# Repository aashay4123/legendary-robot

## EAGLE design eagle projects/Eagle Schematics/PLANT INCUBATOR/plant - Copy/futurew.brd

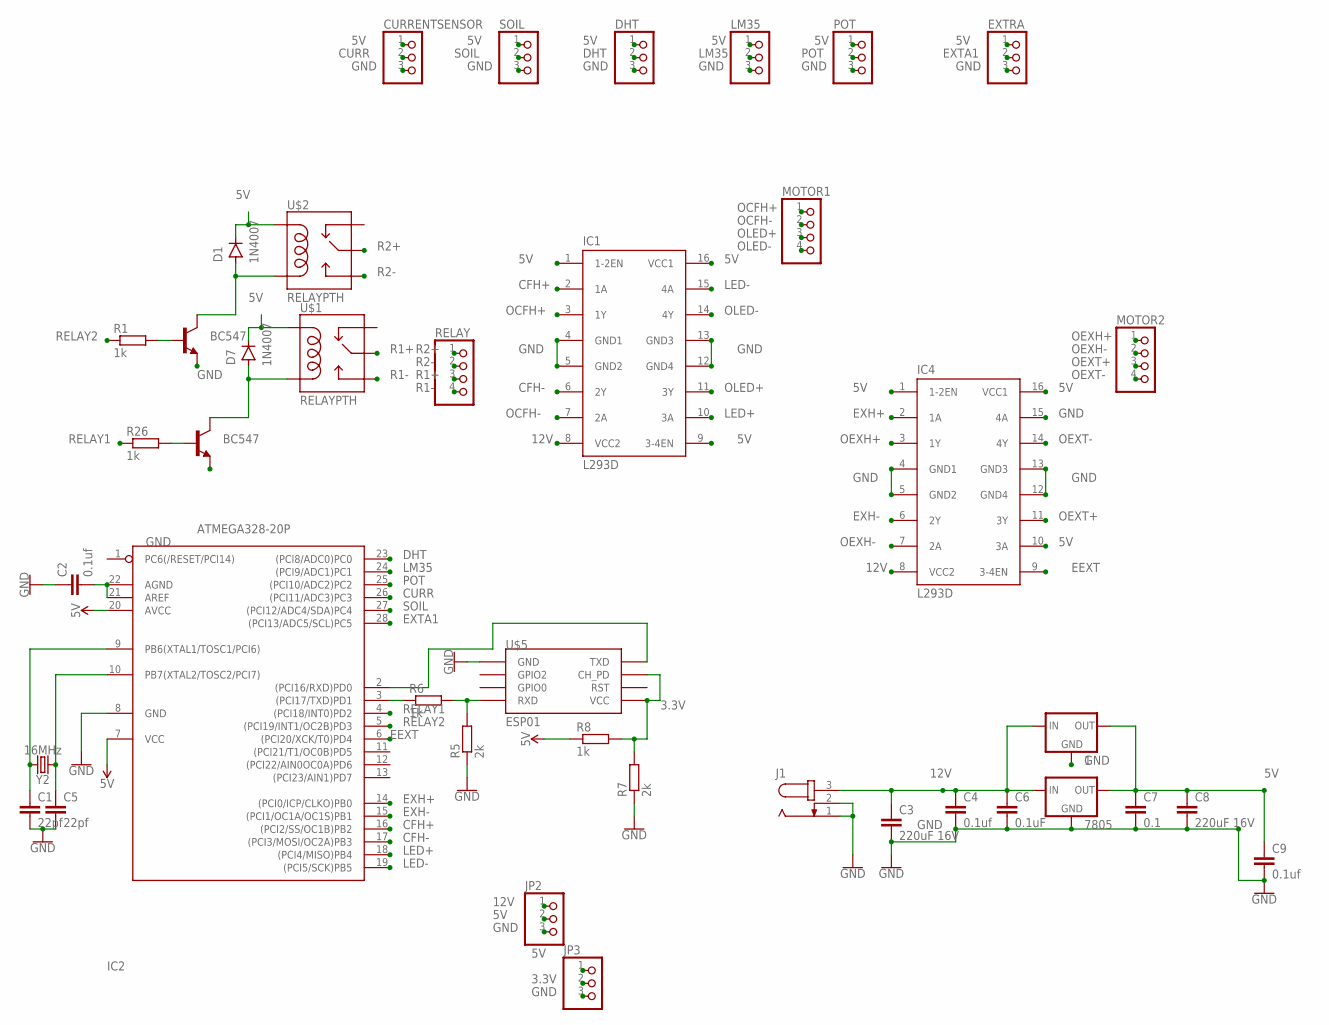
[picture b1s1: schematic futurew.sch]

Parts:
1, 7805: 78XXL
C1, C5: 22pf; C2.5-3
C2, C4, C9: 0.1uf; C2.5-3
C3, C8: 220uF 16V; C2.5-3
C6: 0.1uF; C2.5-3
C7: 0.1; C2.5-3
CURRENTSENSOR: PINHD-1X3; 1X03
D1, D7: 1N4007; DO-41
DHT: PINHD-1X3; 1X03
EXTRA: PINHD-1X3; 1X03
IC1, IC4: L293D; DIL16
IC2: ATMEGA328-20P; DIL28-3
J1: JACK-PLUG1; SPC4078
JP2, JP3: PINHD-1X3; 1X03
LM35: PINHD-1X3; 1X03
MOTOR1, MOTOR2: PINHD-1X4; 1X04
POT: PINHD-1X3; 1X03
R1, R6, R8, R26: 1k; 0204/5
R5, R7: 2k; 0204/5
RELAY: PINHD-1X4; 1X04
SOIL: PINHD-1X3; 1X03
T1, T3: BC547; TO92
U$1, U$2: RELAYPTH; SRD-05VDC-SL-C
U$5: ESP01
Y2: 16MHz; HC49US

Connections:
3.3V: JP3.2, R7.2, R8.2, U$5.CH_PD, U$5.VCC
5V: 1.OUT, 7805.OUT, C7.1, C8.1, C9.1, CURRENTSENSOR.1, D1.C, D7.C, DHT.1, EXTRA.1, IC1.1 (1-2EN), IC1.9 (3-4EN), IC1.16 (VCC1), IC2.7 (VCC), IC2.20 (AVCC), IC4.1 (1-2EN), IC4.10 (3A), IC4.16 (VCC1), JP2.2, JP3.1, LM35.1, POT.1, R8.1, SOIL.1, U$1.COIL1, U$2.COIL1
12V: 1.IN, 7805.IN, C3.1, C4.1, C6.1, IC1.8 (VCC2), IC4.8 (VCC2), J1.3, JP2.1
CFH+: IC1.2 (1A), IC2.16 ((PCI2/SS/OC1B)PB2)
CFH-: IC1.6 (2Y), IC2.17 ((PCI3/MOSI/OC2A)PB3)
CURR: CURRENTSENSOR.2, IC2.26 ((PCI11/ADC3)PC3)
DHT: DHT.2, IC2.23 ((PCI8/ADC0)PC0)
EEXT: IC2.6 ((PCI20/XCK/T0)PD4), IC4.9 (3-4EN)
EXH+: IC2.14 ((PCI0/ICP/CLKO)PB0), IC4.2 (1A)
EXH-: IC2.15 ((PCI1/OC1A/OC1S)PB1), IC4.6 (2Y)
EXTA1: EXTRA.2, IC2.28 ((PCI13/ADC5/SCL)PC5)
GND: 1.GND, 7805.GND, C1.2, C2.1, C3.2, C4.2, C5.2, C6.2, C7.2, C8.2, C9.2, CURRENTSENSOR.3, DHT.3, EXTRA.3, IC1.4 (GND1), IC1.5 (GND2), IC1.12 (GND4), IC1.13 (GND3), IC2.8 (GND), IC4.4 (GND1), IC4.5 (GND2), IC4.12 (GND4), IC4.13 (GND3), IC4.15 (4A), J1.1, J1.2, JP2.3, JP3.3, LM35.3, POT.3, R5.1, R7.1, SOIL.3, T1.1 (E), T3.1 (E), U$5.GND
LED+: IC1.10 (3A), IC2.18 ((PCI4/MISO)PB4)
LED-: IC1.15 (4A), IC2.19 ((PCI5/SCK)PB5)
LM35: IC2.24 ((PCI9/ADC1)PC1), LM35.2
unnamed: R5.2, R6.2, U$5.RX (RXD)
unnamed: IC2.3 ((PCI17/TXD)PD1), R6.1
unnamed: IC2.2 ((PCI16/RXD)PD0), U$5.TX (TXD)
unnamed: D7.A, T3.3 (C), U$1.COIL0
unnamed: R1.2, T1.2 (B)
unnamed: D1.A, T1.3 (C), U$2.COIL0
unnamed: C2.2, IC2.21 (AREF), IC2.22 (AGND)
unnamed: R26.2, T3.2 (B)
unnamed: C5.1, IC2.10 (PB7(XTAL2/TOSC2/PCI7)), Y2.1
unnamed: C1.1, IC2.9 (PB6(XTAL1/TOSC1/PCI6)), Y2.2
OCFH+: IC1.3 (1Y), MOTOR1.1
OCFH-: IC1.7 (2A), MOTOR1.2
OEXH+: IC4.3 (1Y), MOTOR2.1
OEXH-: IC4.7 (2A), MOTOR2.2
OEXT+: IC4.11 (3Y), MOTOR2.3
OEXT-: IC4.14 (4Y), MOTOR2.4
OLED+: IC1.11 (3Y), MOTOR1.3
OLED-: IC1.14 (4Y), MOTOR1.4
POT: IC2.25 ((PCI10/ADC2)PC2), POT.2
R1+: RELAY.3, U$1.SWCOMMON
R1-: RELAY.4, U$1.SWOPEN
R2+: RELAY.1, U$2.SWCOMMON
R2-: RELAY.2, U$2.SWOPEN
RELAY1: IC2.4 ((PCI18/INT0)PD2), R26.1
RELAY2: IC2.5 ((PCI19/INT1/OC2B)PD3), R1.1
SOIL: IC2.27 ((PCI12/ADC4/SDA)PC4), SOIL.2

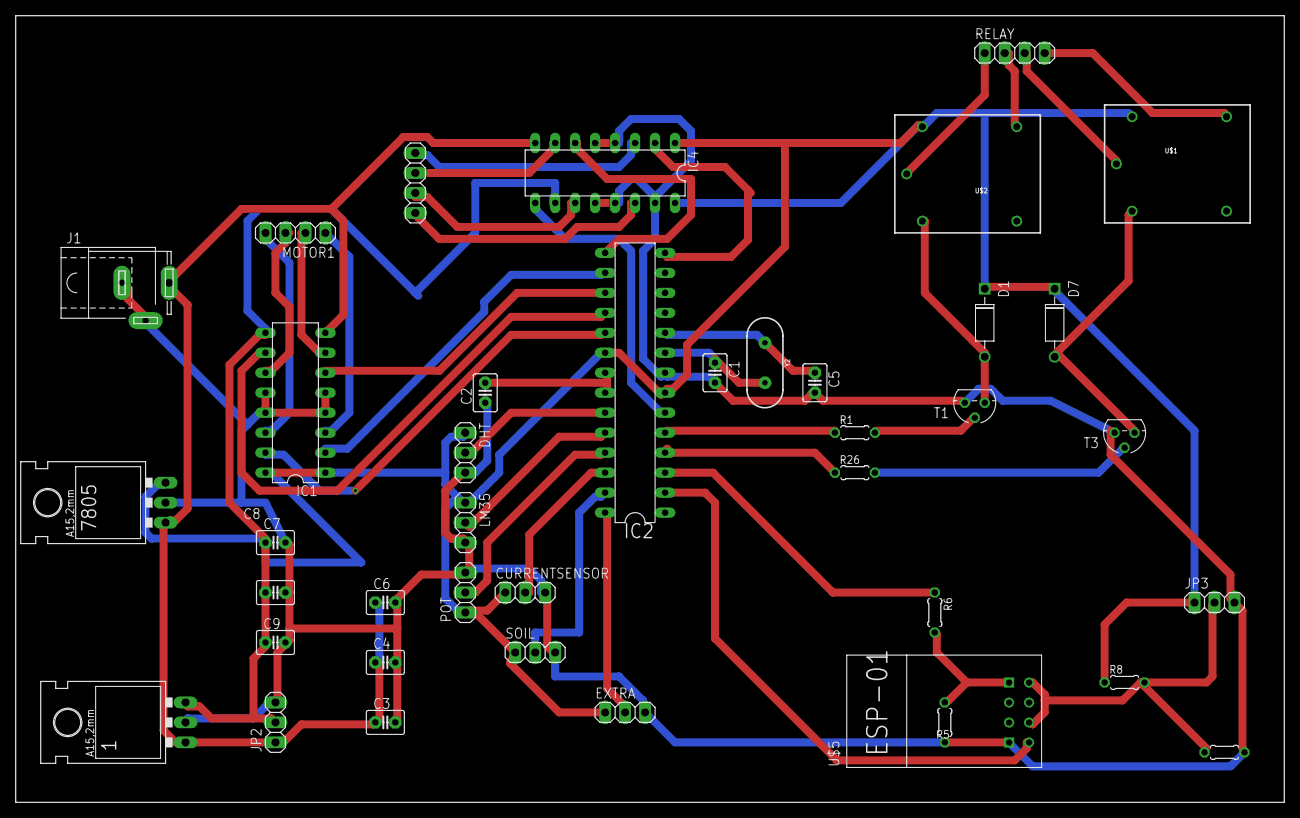
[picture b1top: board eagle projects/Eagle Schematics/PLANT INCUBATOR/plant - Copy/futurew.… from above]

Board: 2 copper layers, 161.3 x 100.0 mm, 40 parts (0 on the bottom side), 41 nets.

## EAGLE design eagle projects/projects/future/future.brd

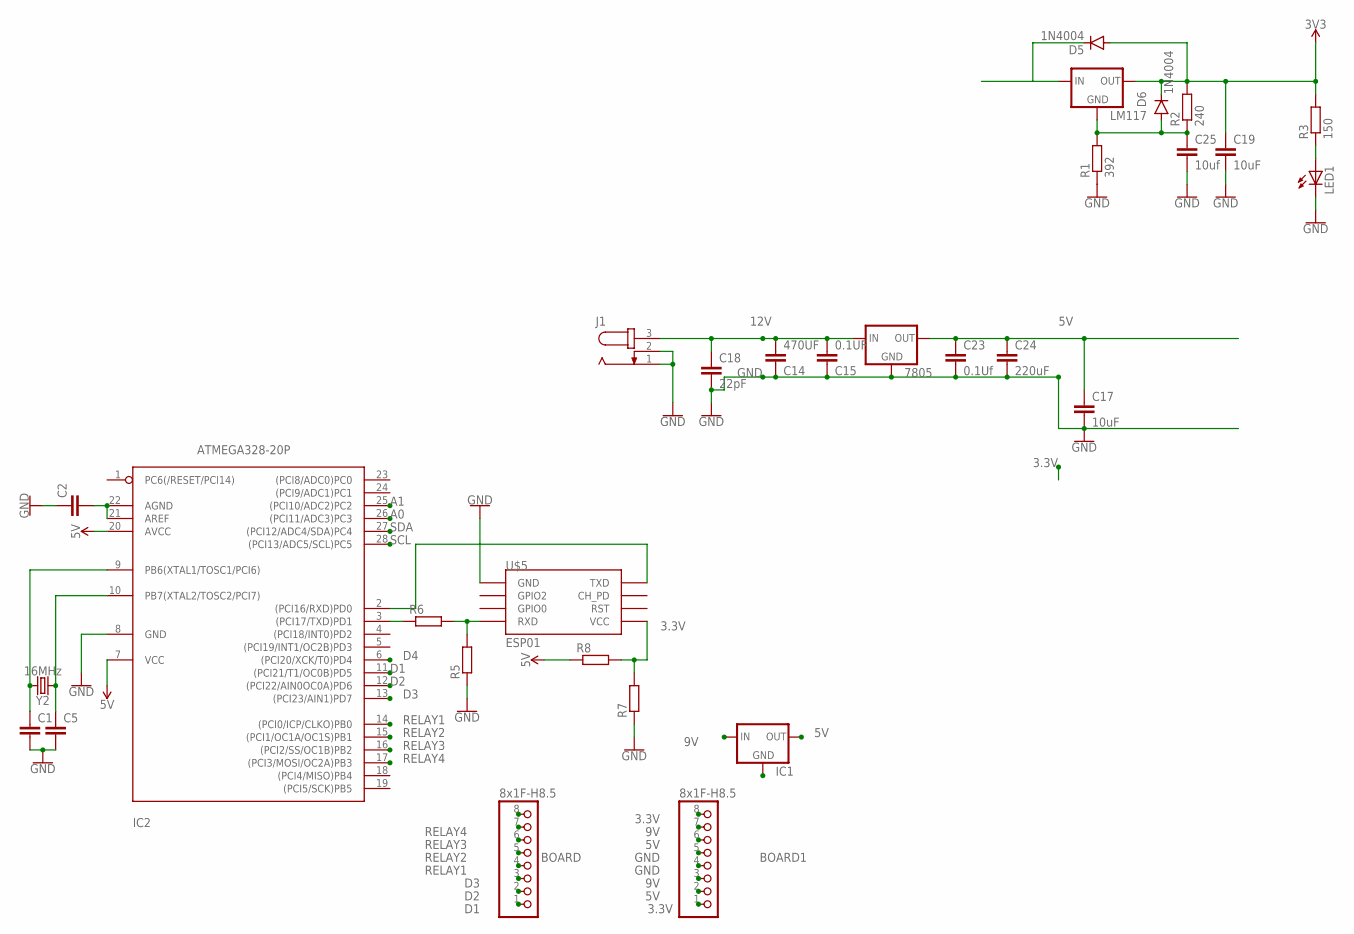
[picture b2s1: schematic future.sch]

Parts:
7805: 78XXL
BOARD, BOARD1: 8x1F-H8.5; 1X08
C1, C2, C5: C2,5-3; C2.5-3
C14: 470UF; 0603
C15: 0.1UF; 0603
C17, C19: 10uF; 0603
C18: 22pF; 0603
C23: 0.1Uf; 0603
C24: 220uF; 0603
C25: 10uf; 0603
D5, D6: 1N4004; DO41-10
IC1: 78LXX
IC2: ATMEGA328-20P; DIL28-3
J1: JACK-PLUG1; SPC4078
LED1: LED5MM
LM117: 78XXL
R1: 392; 0204/5
R2: 240; 0204/5
R3: 150; 0204/5
R5, R6, R7, R8: R-EU_0204/5; 0204/5
U$5: ESP01
Y2: 16MHz; HC49US

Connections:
3.3V: BOARD1.1, BOARD1.8, R7.2, R8.2, U$5.VCC
5V: 7805.OUT, BOARD1.2, BOARD1.6, C17.1, C19.1, C23.1, C24.1, D5.A, D5.C, D6.C, IC1.OUT, IC2.7 (VCC), IC2.20 (AVCC), LM117.IN, LM117.OUT, R2.2, R3.2, R8.1
9V: BOARD1.3, BOARD1.7, IC1.IN
12V: 7805.IN, C14.1, C15.1, C18.1, J1.3
A0: IC2.26 ((PCI11/ADC3)PC3)
A1: IC2.25 ((PCI10/ADC2)PC2)
D1: BOARD.1, IC2.11 ((PCI21/T1/OC0B)PD5)
D2: BOARD.2, IC2.12 ((PCI22/AIN0OC0A)PD6)
D3: BOARD.3, IC2.13 ((PCI23/AIN1)PD7)
D4: BOARD.8, IC2.6 ((PCI20/XCK/T0)PD4)
GND: 7805.GND, BOARD1.4, BOARD1.5, C1.2, C2.1, C5.2, C14.2, C15.2, C17.2, C18.2, C19.2, C23.2, C24.2, C25.2, IC1.GND, IC2.8 (GND), J1.1, J1.2, LED1.K (C), R1.1, R5.1, R7.1, U$5.GND
unnamed: R5.2, R6.2, U$5.RX (RXD)
unnamed: IC2.3 ((PCI17/TXD)PD1), R6.1
unnamed: IC2.2 ((PCI16/RXD)PD0), U$5.TX (TXD)
unnamed: C2.2, IC2.21 (AREF), IC2.22 (AGND)
unnamed: C25.1, D6.A, LM117.GND, R1.2, R2.1
unnamed: C5.1, IC2.10 (PB7(XTAL2/TOSC2/PCI7)), Y2.1
unnamed: C1.1, IC2.9 (PB6(XTAL1/TOSC1/PCI6)), Y2.2
unnamed: LED1.A, R3.1
RELAY1: BOARD.4, IC2.14 ((PCI0/ICP/CLKO)PB0)
RELAY2: BOARD.5, IC2.15 ((PCI1/OC1A/OC1S)PB1)
RELAY3: BOARD.6, IC2.16 ((PCI2/SS/OC1B)PB2)
RELAY4: BOARD.7, IC2.17 ((PCI3/MOSI/OC2A)PB3)
SCL: IC2.28 ((PCI13/ADC5/SCL)PC5)
SDA: IC2.27 ((PCI12/ADC4/SDA)PC4)

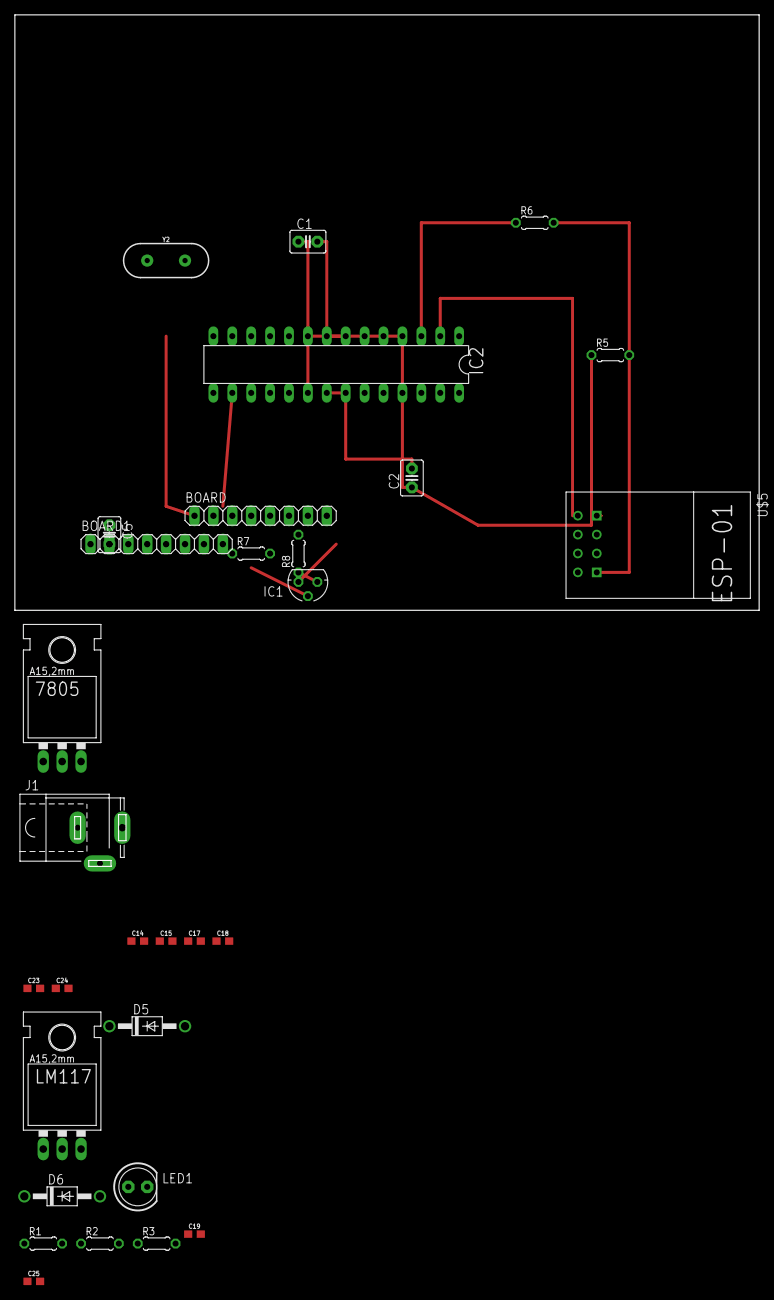
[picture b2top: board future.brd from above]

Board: 2 copper layers, 30 parts (0 on the bottom side), 21 nets.

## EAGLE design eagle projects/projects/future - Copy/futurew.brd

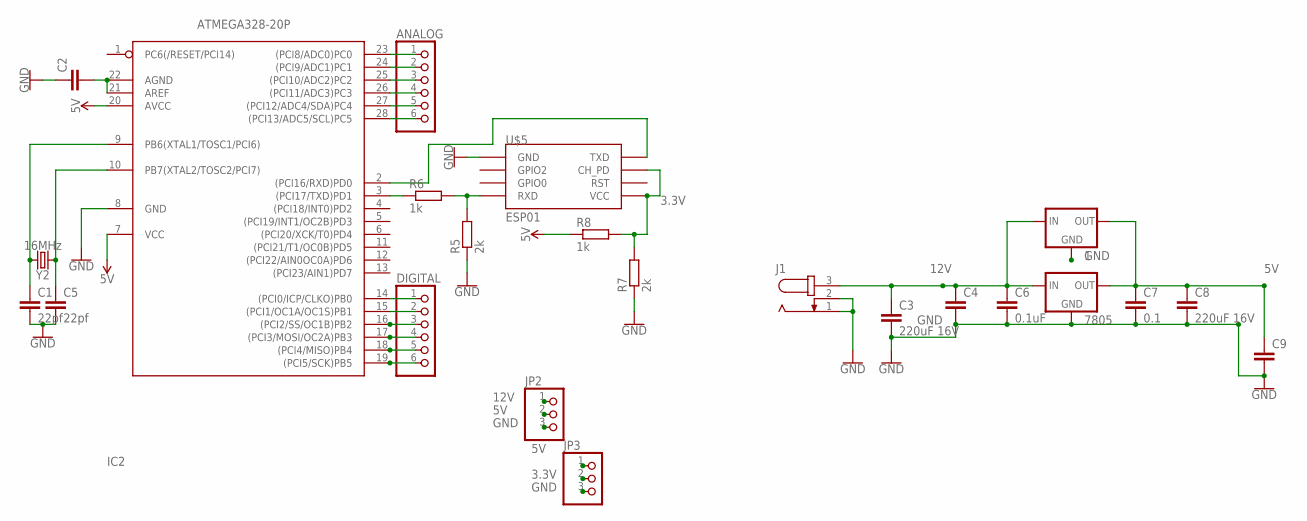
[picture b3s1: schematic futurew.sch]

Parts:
1, 7805: 78XXL
ANALOG: PINHD-1X6; 1X06
C1, C5: 22pf; C2.5-3
C2, C4, C9: C2,5-3; C2.5-3
C3, C8: 220uF 16V; C2.5-3
C6: 0.1uF; C2.5-3
C7: 0.1; C2.5-3
DIGITAL: PINHD-1X6; 1X06
IC2: ATMEGA328-20P; DIL28-3
J1: JACK-PLUG1; SPC4078
JP2, JP3: PINHD-1X3; 1X03
R5, R7: 2k; 0204/5
R6, R8: 1k; 0204/5
U$5: ESP01
Y2: 16MHz; HC49US

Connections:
3.3V: JP3.2, R7.2, R8.2, U$5.CH_PD, U$5.VCC
5V: 1.OUT, 7805.OUT, C7.1, C8.1, C9.1, IC2.7 (VCC), IC2.20 (AVCC), JP2.2, JP3.1, R8.1
12V: 1.IN, 7805.IN, C3.1, C4.1, C6.1, J1.3, JP2.1
GND: 1.GND, 7805.GND, C1.2, C2.1, C3.2, C4.2, C5.2, C6.2, C7.2, C8.2, C9.2, IC2.8 (GND), J1.1, J1.2, JP2.3, JP3.3, R5.1, R7.1, U$5.GND
unnamed: R5.2, R6.2, U$5.RX (RXD)
unnamed: IC2.3 ((PCI17/TXD)PD1), R6.1
unnamed: IC2.2 ((PCI16/RXD)PD0), U$5.TX (TXD)
unnamed: DIGITAL.6, IC2.19 ((PCI5/SCK)PB5)
unnamed: DIGITAL.5, IC2.18 ((PCI4/MISO)PB4)
unnamed: DIGITAL.4, IC2.17 ((PCI3/MOSI/OC2A)PB3)
unnamed: DIGITAL.3, IC2.16 ((PCI2/SS/OC1B)PB2)
unnamed: ANALOG.1, IC2.23 ((PCI8/ADC0)PC0)
unnamed: ANALOG.2, IC2.24 ((PCI9/ADC1)PC1)
unnamed: ANALOG.3, IC2.25 ((PCI10/ADC2)PC2)
unnamed: C2.2, IC2.21 (AREF), IC2.22 (AGND)
unnamed: ANALOG.4, IC2.26 ((PCI11/ADC3)PC3)
unnamed: ANALOG.5, IC2.27 ((PCI12/ADC4/SDA)PC4)
unnamed: ANALOG.6, IC2.28 ((PCI13/ADC5/SCL)PC5)
unnamed: DIGITAL.1, IC2.14 ((PCI0/ICP/CLKO)PB0)
unnamed: DIGITAL.2, IC2.15 ((PCI1/OC1A/OC1S)PB1)
unnamed: C5.1, IC2.10 (PB7(XTAL2/TOSC2/PCI7)), Y2.1
unnamed: C1.1, IC2.9 (PB6(XTAL1/TOSC1/PCI6)), Y2.2

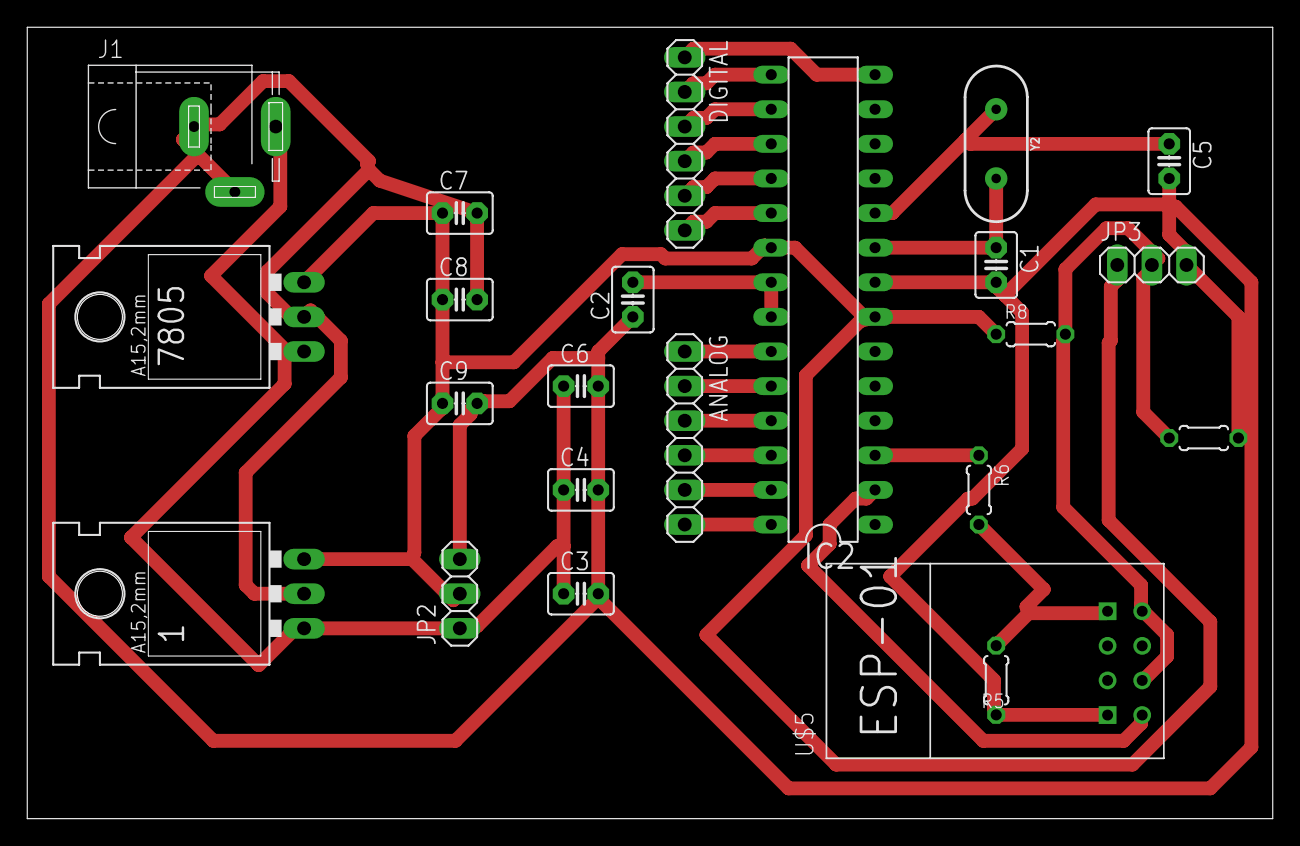
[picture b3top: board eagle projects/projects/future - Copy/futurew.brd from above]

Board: 2 copper layers, 91.4 x 58.1 mm, 23 parts (0 on the bottom side), 22 nets.

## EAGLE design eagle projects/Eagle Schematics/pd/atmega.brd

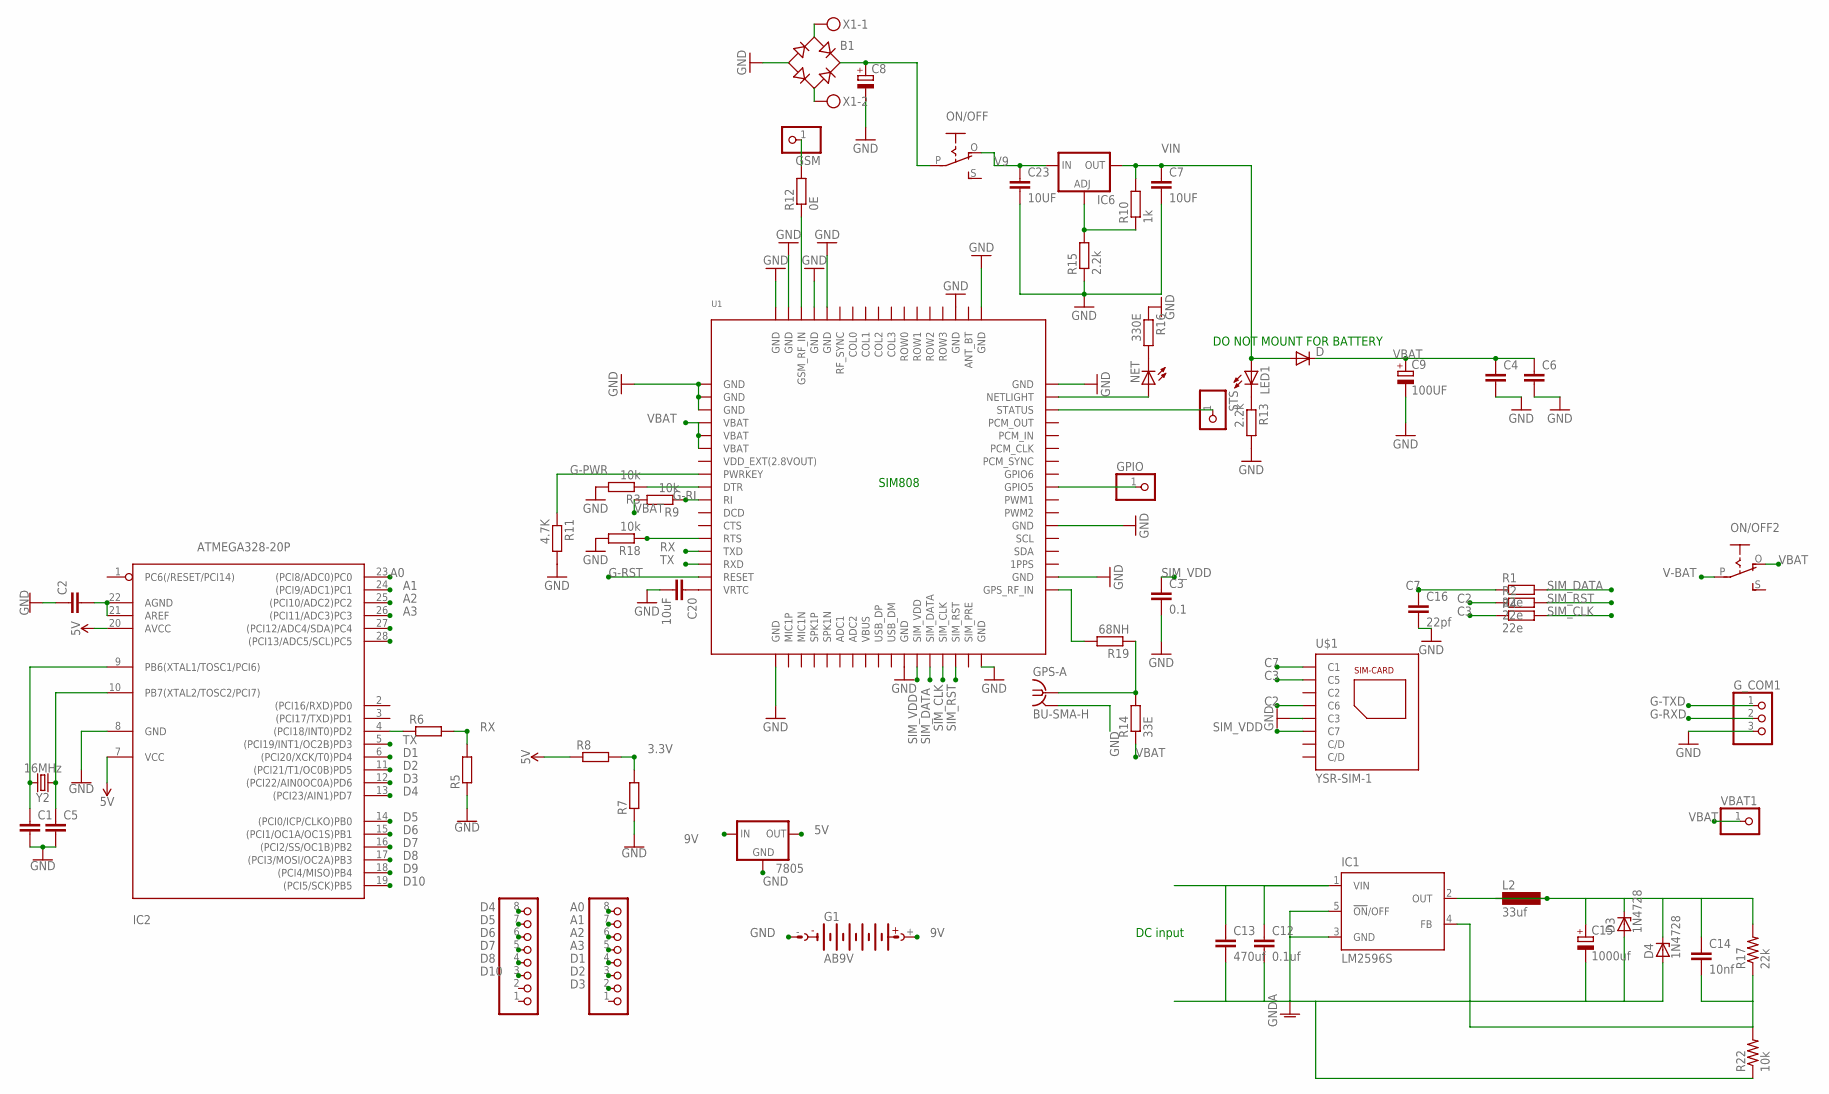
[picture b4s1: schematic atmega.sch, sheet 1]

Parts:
7805: 78LXX
B1: RB1A
BOARD, BOARD1: 8x1F-H8.5; 1X08
C1, C2, C5: C2,5-3; C2.5-3
C3: 0.1; C1206
C4, C6: C-EUC1206; C1206
C7: 10UF; C1206K
C8: CPOL-EUE5-10.5; E5-10,5
C9: 100UF; E3,5-8
C12: 0.1uf; C2.5-3
C13: 470uf; C2.5-3
C14: 10nf; C2.5-3
C15: 1000uf; 085CS_1AR
C16: 22pf; C1206
C20: 10uF; C1206K
C23: 10UF; C1206
D: DO41-10
D3, D4: 1N4728; DO41Z10
G1: AB9V
GPIO: PINHD-1X1; 1X01
GPS-A: BU-SMA-H
GSM: PINHD-1X1; 1X01
G_COM1: PINHD-1X3; 1X03
IC1: LM2596S; TO263-5
IC2: ATMEGA328-20P; DIL28-3
IC6: LM317TS; 317TS
L2: 33uf; BS11
LED1: LEDCHIPLED_1206; CHIPLED_1206
NET: LEDCHIPLED_1206; CHIPLED_1206
ON/OFF, ON/OFF2: EG1218S; EG1218
R1: 22e; M1206
R2, R4: 22e; R1206
R3, R9, R18: 10k; R1206
R5, R6, R7, R8: R-EU_0204/5; 0204/5
R10: 1k; R1206
R11: 4.7K; R1206
R12: 0E; R1206
R13, R15: 2.2k; R1206
R14: 33E; R1206
R16: 330E; R1206
R17: 22k; 0204V
R19: 68NH; R1206
R22: 10k; 0204V
STS: PINHD-1X1; 1X01
U1: GSM_SIM808_LITERAL; SIM900_SMT
U$1: YSR-SIM-1; 5036_006_200_862
VBAT1: PINHD-1X1; 1X01
X1: MKDSN1,5/2-5,08
Y2: 16MHz; HC49US

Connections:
3.3V: R7.2, R8.2
5V: 7805.OUT, IC2.7 (VCC), IC2.20 (AVCC), R8.1
9V: 7805.IN, G1.+
A0: BOARD1.8, IC2.23 ((PCI8/ADC0)PC0)
A1: BOARD1.7, IC2.24 ((PCI9/ADC1)PC1)
A2: BOARD1.6, IC2.25 ((PCI10/ADC2)PC2)
A3: BOARD1.5, IC2.26 ((PCI11/ADC3)PC3)
C2: R2.1, U$1.C6
C3: R4.1, U$1.C5
C7: C16.1, R1.1, U$1.C1
D1: BOARD1.4, IC2.6 ((PCI20/XCK/T0)PD4)
D2: BOARD1.3, IC2.11 ((PCI21/T1/OC0B)PD5)
D3: BOARD1.2, IC2.12 ((PCI22/AIN0OC0A)PD6)
D4: BOARD.8, IC2.13 ((PCI23/AIN1)PD7)
D5: BOARD.7, IC2.14 ((PCI0/ICP/CLKO)PB0)
D6: BOARD.6, IC2.15 ((PCI1/OC1A/OC1S)PB1)
D7: BOARD.5, IC2.16 ((PCI2/SS/OC1B)PB2)
D8: BOARD.4, IC2.17 ((PCI3/MOSI/OC2A)PB3)
D9: IC2.18 ((PCI4/MISO)PB4)
D10: BOARD.3, IC2.19 ((PCI5/SCK)PB5)
G-PWR: R11.1, U1.P$8 (PWRKEY)
G-RI: R9.1, U1.P$10 (RI)
G-RST: U1.P$16 (RESET)
G-RXD: G_COM1.2
G-TXD: G_COM1.1
GND: 7805.GND, B1.-, C1.2, C2.1, C3.2, C4.2, C5.2, C6.2, C7.2, C8.-, C9.-, C16.2, C20.2, C23.2, G1.-, GPS-A.2, GPS-A.3 (2), GPS-A.4 (2), GPS-A.5 (2), G_COM1.3, IC2.8 (GND), R3.2, R5.1, R7.1, R11.2, R13.2, R15.1, R16.1, R18.2, U1.P$1 (GND), U1.P$2 (GND), U1.P$3 (GND), U1.P$18 (GND), U1.P$28 (GND), U1.P$34 (GND), U1.P$36 (GND), U1.P$40 (GND), U1.P$51 (GND), U1.P$52 (GND), U1.P$54 (GND), U1.P$64 (GND), U1.P$65 (GND), U1.P$67 (GND), U1.P$68 (GND), U$1.C3
GNDA: C12.2, C13.2, C15.-, D3.A, D4.A, IC1.3 (GND), IC1.5 (!ON!/OFF), R22.1
unnamed: IC2.4 ((PCI18/INT0)PD2), R6.1
unnamed: GPS-A.1, R14.2, R19.1
unnamed: R3.1, U1.P$9 (DTR)
unnamed: NET.A, U1.P$50 (NETLIGHT)
unnamed: STS.1, U1.P$49 (STATUS)
unnamed: R18.1, U1.P$13 (RTS)
unnamed: NET.C, R16.2
unnamed: C2.2, IC2.21 (AREF), IC2.22 (AGND)
unnamed: B1.+, C8.+, ON/OFF.P
unnamed: B1.AC1, X1.1
unnamed: GPIO.1, U1.P$43 (GPIO5)
unnamed: C14.1, C15.+, D3.C, D4.C, IC1.2 (OUT), L2.1, L2.2, R17.2
unnamed: C20.1, U1.P$17 (VRTC)
unnamed: B1.AC2, X1.2
unnamed: C14.2, IC1.4 (FB), R17.1, R22.2
unnamed: C12.1, C13.1, IC1.1 (VIN)
unnamed: GSM.1, R12.2
unnamed: LED1.C, R13.1
unnamed: R12.1, U1.P$66 (GSM_RF_IN)
unnamed: R19.2, U1.P$35 (GPS_RF_IN)
unnamed: C5.1, IC2.10 (PB7(XTAL2/TOSC2/PCI7)), Y2.1
unnamed: IC6.1 (ADJ), R10.1, R15.2
unnamed: C1.1, IC2.9 (PB6(XTAL1/TOSC1/PCI6)), Y2.2
RX: R5.2, R6.2, U1.P$14 (TXD)
SCL: IC2.28 ((PCI13/ADC5/SCL)PC5)
SIM_CLK: R4.2, U1.P$31 (SIM_CLK)
SIM_DATA: R1.2, U1.P$30 (SIM_DATA)
SIM_RST: R2.2, U1.P$32 (SIM_RST)
SIM_VDD: C3.1, U1.P$29 (SIM_VDD), U$1.C7
TX: IC2.5 ((PCI19/INT1/OC2B)PD3), U1.P$15 (RXD)
V9: C23.1, IC6.3 (IN), ON/OFF.O
V-BAT: ON/OFF2.P
VBAT: C4.1, C6.1, C9.+, D.C, ON/OFF2.O, R9.2, R14.1, U1.P$4 (VBAT), U1.P$5 (VBAT), U1.P$6 (VBAT), VBAT1.1
VBUS: U1.P$25 (VBUS)
VDD_EXT(2.8VOUT): U1.P$7 (VDD_EXT(2.8VOUT))
VIN: C7.1, D.A, IC6.2 (OUT), LED1.A, R10.2

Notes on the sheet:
SIM808
DO NOT MOUNT FOR BATTERY
DC input

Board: 2 copper layers, 62 parts (0 on the bottom side), 55 nets, no tracks yet.

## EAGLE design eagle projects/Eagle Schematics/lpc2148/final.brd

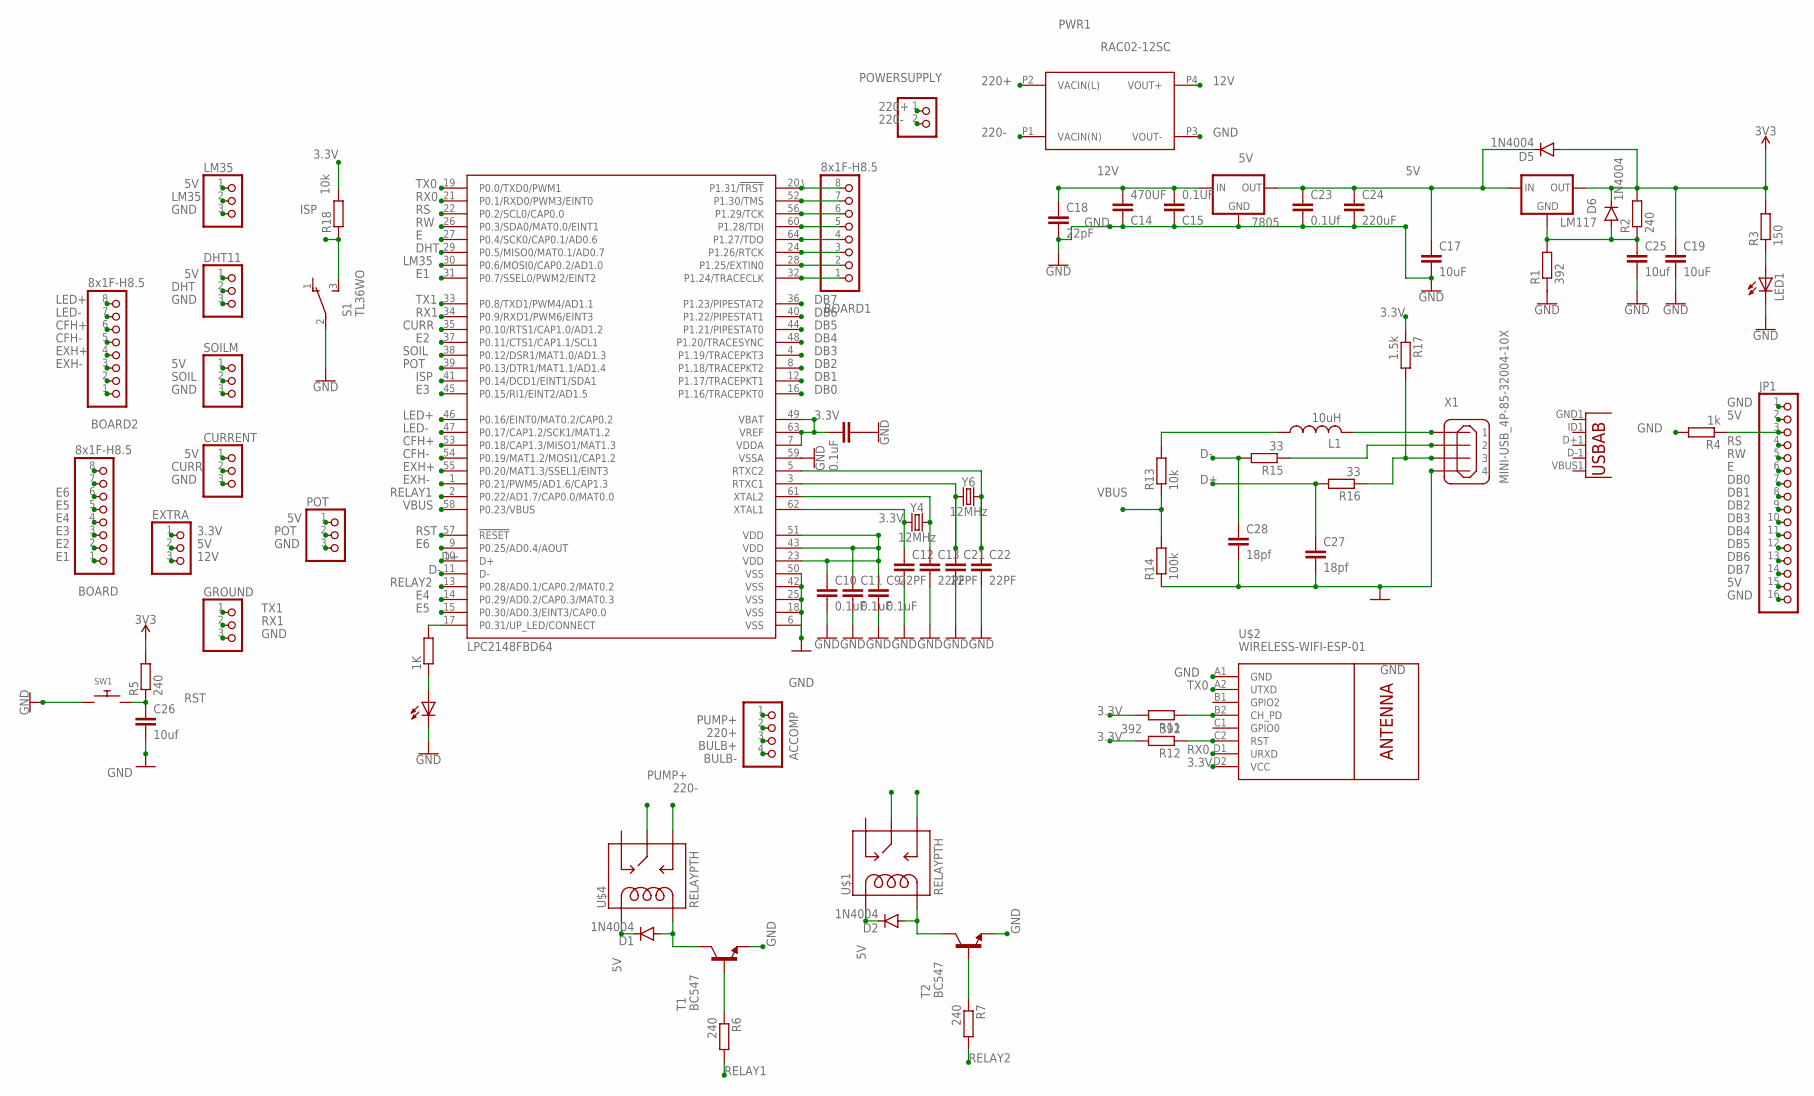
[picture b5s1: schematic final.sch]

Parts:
1K: 1k; 0204/5
7805: 5V; 78XXL
ACCOMP: PINHD-1X4; 1X04
BOARD, BOARD1, BOARD2: 8x1F-H8.5; 1X08
C9, C10, C11, C16: 0.1uF; 0603
C12, C13, C21, C22: 22PF; 0603
C14: 470UF; 0603
C15: 0.1UF; 0603
C17, C19: 10uF; 0603
C18: 22pF; 0603
C23: 0.1Uf; 0603
C24: 220uF; 0603
C25, C26: 10uf; 0603
C27, C28: 18pf; 0603
CURRENT: PINHD-1X3; 1X03
D1, D2, D5, D6: 1N4004; DO41-10
DHT11: PINHD-1X3; 1X03
EXTRA: PINHD-1X3; 1X03
GROUND: PINHD-1X3; 1X03
JP1: PINHD-1X16; 1X16
L1: 10uH; 0204/5
LED1, LED2: LED5MM
LM35: PINHD-1X3; 1X03
LM117: 78XXL
POT: PINHD-1X3; 1X03
POWERSUPPLY: PINHD-1X2; 1X02
PWR1: RAC02-12SC; LOW_PROFILE_POWER_MODULE
R1, R11, R12: 392; 0204/5
R2, R5, R6, R7: 240; 0204/5
R3: 150; 0204/5
R4: 1k; 0204/5
R13, R18: 10k; 0204/5
R14: 100k; 0204/5
R15, R16: 33; 0204/5
R17: 1.5k; 0204/5
S1: TL36WO; TL3XWO
SOILM: PINHD-1X3; 1X03
SW1: SWITCH_PUSHBUTTONC&K_KSS; BTN_CK_KSS
T1, T2: BC547; TO92
U1: LPC2148FBD64; TSQFP50P1200X1200X160-64N
U2: USB""; USB-MICRO-SMD
U$1, U$4: RELAYPTH; SRD-05VDC-SL-C
U$2: WIRELESS-WIFI-ESP-01
X1: MINI-USB_4P-85-32004-10X; 85-32004-10X
Y4, Y6: 12MHz; HC49US

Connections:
3.3V: C9.1, C10.1, C11.1, C16.2, EXTRA.1, R11.2, R12.2, R17.1, R18.2, U1.7 (VDDA), U1.23 (VDD), U1.43 (VDD), U1.49 (VBAT), U1.51 (VDD), U1.63 (VREF), U$2.D2 (VCC)
5V: 7805.OUT, C17.1, C19.1, C23.1, C24.1, CURRENT.1, D1.C, D2.C, D5.A, D5.C, D6.C, DHT11.1, EXTRA.2, JP1.2, JP1.15, LM35.1, LM117.IN, LM117.OUT, POT.1, R2.2, R3.2, R5.2, SOILM.1, U$1.COIL1, U$4.COIL1
12V: 7805.IN, C14.1, C15.1, C18.1, EXTRA.3, PWR1.P4 (VOUT+)
220+: ACCOMP.2, POWERSUPPLY.1, PWR1.P2 (VACIN(L))
220-: POWERSUPPLY.2, PWR1.P1 (VACIN(N)), U$4.SWOPEN
BULB+: ACCOMP.3, U$1.SWCOMMON
BULB-: ACCOMP.4
CFH+: BOARD2.6, U1.53 (P0.18/CAP1.3/MISO1/MAT1.3)
CFH-: BOARD2.5, U1.54 (P0.19/MAT1.2/MOSI1/CAP1.2)
CURR: CURRENT.2, U1.35 (P0.10/RTS1/CAP1.0/AD1.2)
D+: C27.1, R16.2, U1.10 (D+)
D-: C28.1, R15.2, U1.11 (D-)
DB0: JP1.7, U1.16 (P1.16/TRACEPKT0)
DB1: JP1.8, U1.12 (P1.17/TRACEPKT1)
DB2: JP1.9, U1.8 (P1.18/TRACEPKT2)
DB3: JP1.10, U1.4 (P1.19/TRACEPKT3)
DB4: JP1.11, U1.48 (P1.20/TRACESYNC)
DB5: JP1.12, U1.44 (P1.21/PIPESTAT0)
DB6: JP1.13, U1.40 (P1.22/PIPESTAT1)
DB7: JP1.14, U1.36 (P1.23/PIPESTAT2)
DHT: DHT11.2, U1.29 (P0.5/MISO0/MAT0.1/AD0.7)
E: JP1.6, U1.27 (P0.4/SCK0/CAP0.1/AD0.6)
E1: BOARD.1, U1.31 (P0.7/SSEL0/PWM2/EINT2)
E2: BOARD.2, U1.37 (P0.11/CTS1/CAP1.1/SCL1)
E3: BOARD.3, U1.45 (P0.15/RI1/EINT2/AD1.5)
E4: BOARD.4, U1.14 (P0.29/AD0.2/CAP0.3/MAT0.3)
E5: BOARD.5, U1.15 (P0.30/AD0.3/EINT3/CAP0.0)
E6: BOARD.6, U1.9 (P0.25/AD0.4/AOUT)
EXH+: BOARD2.4, U1.55 (P0.20/MAT1.3/SSEL1/EINT3)
EXH-: BOARD2.3, U1.1 (P0.21/PWM5/AD1.6/CAP1.3)
GND: 7805.GND, C9.2, C10.2, C11.2, C12.2, C13.2, C14.2, C15.2, C16.1, C17.2, C18.2, C19.2, C21.2, C22.2, C23.2, C24.2, C25.2, C26.2, C27.2, C28.2, CURRENT.3, DHT11.3, GROUND.3, JP1.1, JP1.16, LED1.K (C), LED2.K (C), LM35.3, POT.3, PWR1.P3 (VOUT-), R1.1, R4.2, R14.1, S1.2, SOILM.3, SW1.P$1, T1.1 (E), T2.1 (E), U1.6 (VSS), U1.18 (VSS), U1.25 (VSS), U1.42 (VSS), U1.50 (VSS), U1.59 (VSSA), U$2.A1 (GND), X1.4
ISP: R18.1, S1.3 (S), U1.41 (P0.14/DCD1/EINT1/SDA1)
LED+: BOARD2.8, U1.46 (P0.16/EINT0/MAT0.2/CAP0.2)
LED-: BOARD2.7, U1.47 (P0.17/CAP1.2/SCK1/MAT1.2)
LM35: LM35.2, U1.30 (P0.6/MOSI0/CAP0.2/AD1.0)
unnamed: R6.1, T1.2 (B)
unnamed: R7.1, T2.2 (B)
unnamed: D1.A, T1.3 (C), U$4.COIL0
unnamed: D2.A, T2.3 (C), U$1.COIL0
unnamed: C12.1, U1.62 (XTAL1), Y4.1
unnamed: C13.1, U1.61 (XTAL2), Y4.2
unnamed: BOARD1.7, U1.52 (P1.30/TMS)
unnamed: JP1.3, R4.1
unnamed: C21.1, U1.3 (RTXC1), Y6.1
unnamed: C25.1, D6.A, LM117.GND, R1.2, R2.1
unnamed: C22.1, U1.5 (RTXC2), Y6.2
unnamed: LED1.A, R3.1
unnamed: 1K.1, LED2.A
unnamed: 1K.2, U1.17 (P0.31/UP_LED/CONNECT)
unnamed: L1.2, X1.1
unnamed: R15.1, X1.2
unnamed: R16.1, R17.2, X1.3
unnamed: BOARD1.1, U1.32 (P1.24/TRACECLK)
unnamed: BOARD1.2, U1.28 (P1.25/EXTIN0)
unnamed: BOARD1.3, U1.24 (P1.26/RTCK)
unnamed: BOARD1.4, U1.64 (P1.27/TDO)
unnamed: BOARD1.5, U1.60 (P1.28/TDI)
unnamed: L1.1, R13.2
unnamed: BOARD1.6, U1.56 (P1.29/TCK)
unnamed: R11.1, U$2.B2 (CH_PD)
unnamed: R12.1, U$2.C2 (RST)
POT: POT.2, U1.39 (P0.13/DTR1/MAT1.1/AD1.4)
PUMP+: ACCOMP.1, U$4.SWCOMMON
RELAY1: BOARD2.2, R6.2, U1.2 (P0.22/AD1.7/CAP0.0/MAT0.0)
RELAY2: BOARD2.1, R7.2, U1.13 (P0.28/AD0.1/CAP0.2/MAT0.2)
RS: JP1.4, U1.22 (P0.2/SCL0/CAP0.0)
RST: C26.1, R5.1, SW1.P$2, U1.57 (!RESET)
RW: JP1.5, U1.26 (P0.3/SDA0/MAT0.0/EINT1)
RX0: U1.21 (P0.1/RXD0/PWM3/EINT0), U$2.D1 (URXD)
RX1: GROUND.2, U1.34 (P0.9/RXD1/PWM6/EINT3)
SOIL: SOILM.2, U1.38 (P0.12/DSR1/MAT1.0/AD1.3)
TX0: U1.19 (P0.0/TXD0/PWM1), U$2.A2 (UTXD)
TX1: GROUND.1, U1.33 (P0.8/TXD1/PWM4/AD1.1)
VBUS: R13.1, R14.2, U1.58 (P0.23/VBUS)
\: BOARD1.8, U1.20 (P1.31/!TRST)

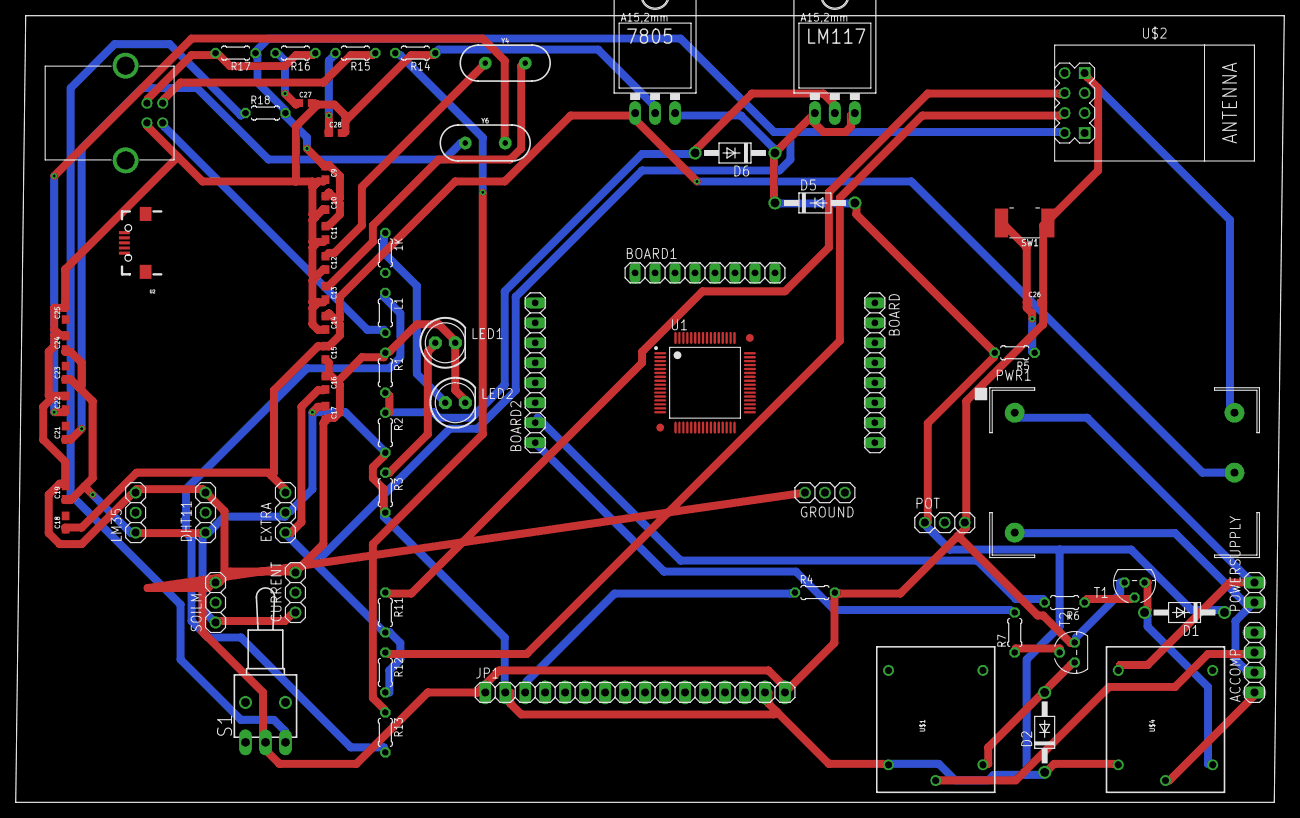
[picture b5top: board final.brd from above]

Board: 2 copper layers, 161.3 x 100.0 mm, 70 parts (0 on the bottom side), 74 nets.

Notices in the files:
parts and their libraries:
SparkFun-Clocks: Licensing: Creative Commons ShareAlike 4.0 International - https://creativecommons.org/licenses/by-sa/4.0
diy-modules: Released under the Creative Commons Attribution 4.0 International License: http://creativecommons.org/licenses/by/4.0
philips-5: Copyright 2006 Weartronics
